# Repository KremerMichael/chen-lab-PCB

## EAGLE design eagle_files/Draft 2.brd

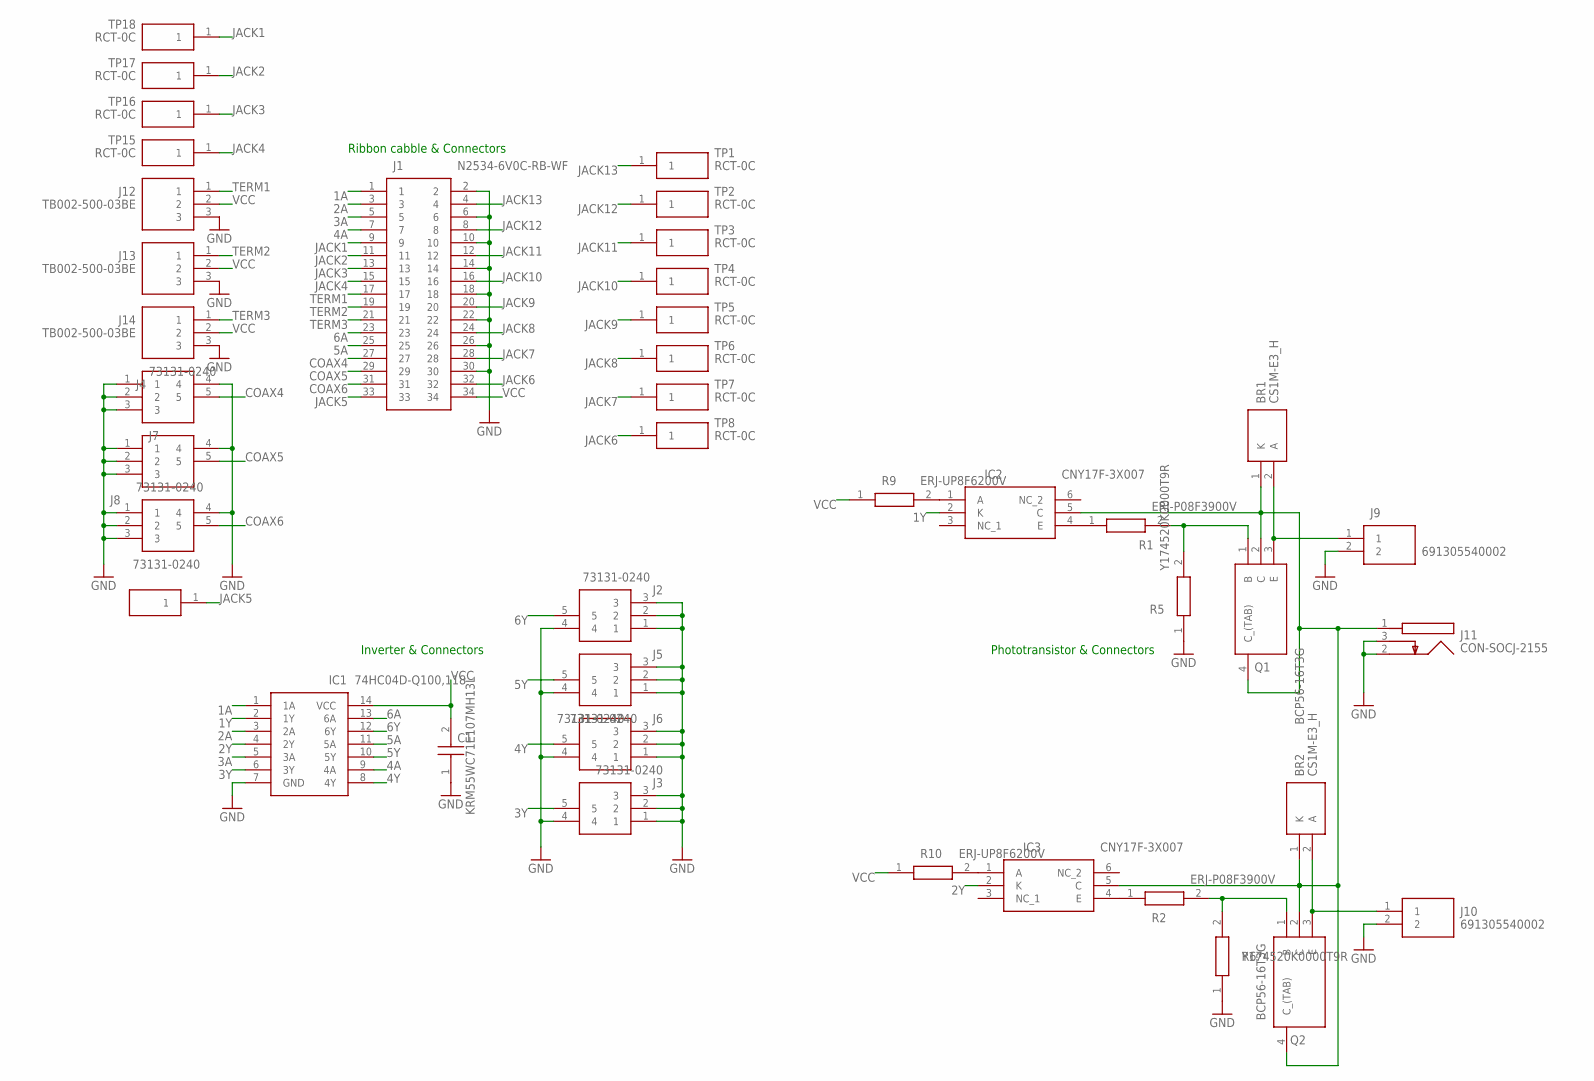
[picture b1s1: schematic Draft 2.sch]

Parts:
BR1, BR2: CS1M-E3_H; DIOM5127X229N
C1: KRM55WC71E107MH13L; CAPC6153X670N
IC1: 74HC04D-Q100,118; SOIC127P600X175-14N
IC2, IC3: CNY17F-3X007; SOP254P1030X440-6N
J1: N2534-6V0C-RB-WF; 3M_N2534-6V0C-RB-WF
J2, J3, J4, J5, J6, J7, J8: 73131-0240; 731310240
J9, J10: 691305540002; SHDRRA2W100P0X508_1X2_1216X120
J11: CON-SOCJ-2155; CONSOCJ2155
J12, J13, J14: TB002-500-03BE; SHDR3W100P0X500_1X3_1500X760X1
Q1, Q2: BCP56-16T3G; SOT230P700X175-4N
R1, R2: ERJ-P08F3900V; RESC3116X70N
R5, R6: Y174520K0000T9R; RESM6032X279N
R9, R10: ERJ-UP8F6200V; RESC3116X70N
TP1, TP2, TP3, TP4, TP5, TP6, TP7, TP8, TP9, TP15, TP16, TP17, TP18: RCT-0C

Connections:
1A: IC1.1 (1A), J1.1
1Y: IC1.2 (1Y), IC2.2 (K)
2A: IC1.3 (2A), J1.3
2Y: IC1.4 (2Y), IC3.2 (K)
3A: IC1.5 (3A), J1.5
3Y: IC1.6 (3Y), J3.5
4A: IC1.9 (4A), J1.7
4Y: IC1.8 (4Y), J6.5
5A: IC1.11 (5A), J1.25
5Y: IC1.10 (5Y), J5.5
6A: IC1.13 (6A), J1.23
6Y: IC1.12 (6Y), J2.5
COAX4: J1.27, J4.5
COAX5: J1.29, J7.5
COAX6: J1.31, J8.5
GND: C1.1, IC1.7 (GND), J1.2, J1.6, J1.10, J1.14, J1.18, J1.22, J1.26, J1.30, J2.1, J2.2, J2.3, J2.4, J3.1, J3.2, J3.3, J3.4, J4.1, J4.2, J4.3, J4.4, J5.1, J5.2, J5.3, J5.4, J6.1, J6.2, J6.3, J6.4, J7.1, J7.2, J7.3, J7.4, J8.1, J8.2, J8.3, J8.4, J9.2, J10.2, J11.2, J11.3, J12.3, J13.3, J14.3, R5.1, R6.1
JACK1: J1.9, TP18.1
JACK2: J1.11, TP17.1
JACK3: J1.13, TP16.1
JACK4: J1.15, TP15.1
JACK5: J1.33, TP9.1
JACK6: J1.32, TP8.1
JACK7: J1.28, TP7.1
JACK8: J1.24, TP6.1
JACK9: J1.20, TP5.1
JACK10: J1.16, TP4.1
JACK11: J1.12, TP3.1
JACK12: J1.8, TP2.1
JACK13: J1.4, TP1.1
unnamed: IC2.1 (A), R9.2
unnamed: BR2.2 (A), J10.1, Q2.3 (E)
unnamed: Q1.1 (B), R1.2, R5.2
unnamed: IC3.1 (A), R10.2
unnamed: IC3.4 (E), R2.1
unnamed: IC2.4 (E), R1.1
unnamed: BR1.2 (A), J9.1, Q1.3 (E)
unnamed: BR1.1 (K), BR2.1 (K), IC2.5 (C), IC3.5 (C), J11.1, Q1.2 (C), Q1.4 (C_(TAB)), Q2.2 (C), Q2.4 (C_(TAB))
unnamed: Q2.1 (B), R2.2, R6.2
TERM1: J1.17, J12.1
TERM2: J1.19, J13.1
TERM3: J1.21, J14.1
VCC: C1.2, IC1.14 (VCC), J1.34, J12.2, J13.2, J14.2, R9.1, R10.1

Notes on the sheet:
Ribbon cabble & Connectors
Inverter & Connectors
Phototransistor & Connectors

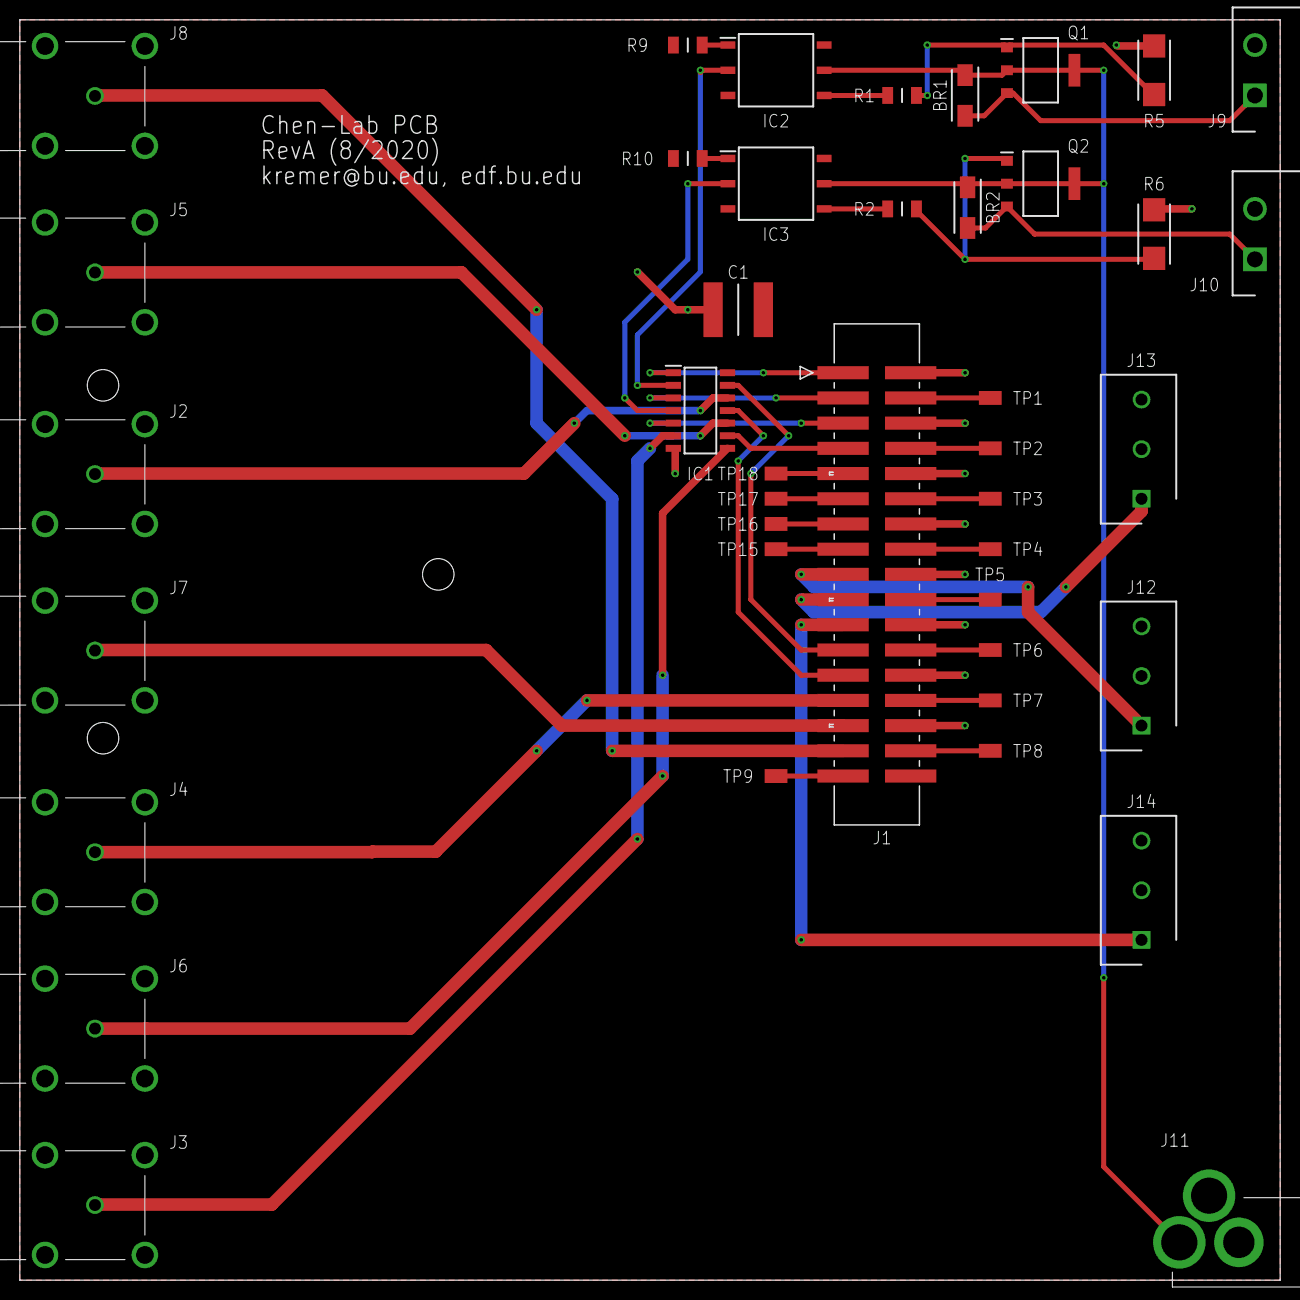
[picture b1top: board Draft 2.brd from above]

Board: 2 copper layers, 127.0 x 127.0 mm, 41 parts (0 on the bottom side), 42 nets.

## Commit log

2020-08-23 started git repo
2020-08-24 auto push run at Mon 24 Aug 2020 01:14:17 AM EDT
2020-08-24 auto push run at Mon 24 Aug 2020 11:25:32 AM EDT
2020-08-24 auto push run at Mon 24 Aug 2020 11:52:34 AM EDT
2020-08-24 auto push run at Mon 24 Aug 2020 11:56:28 AM EDT
2020-08-24 auto push run at Mon 24 Aug 2020 11:58:40 AM EDT
2020-08-24 auto push run at Mon 24 Aug 2020 12:03:22 PM EDT
2020-08-24 auto push run at Mon 24 Aug 2020 12:08:45 PM EDT
2020-08-24 auto push run at Mon 24 Aug 2020 12:14:02 PM EDT
2020-08-24 auto push run at Mon 24 Aug 2020 03:08:45 PM EDT
2020-08-24 auto push run at Mon 24 Aug 2020 03:10:38 PM EDT
2020-08-25 moving to kicad
2020-08-26 auto push run at Tue 25 Aug 2020 09:51:00 PM EDT
2020-08-26 auto push run at Tue 25 Aug 2020 09:53:13 PM EDT
2020-08-26 Add some 3D models
2020-08-26 more 3D models
2020-08-27 3D model for USB thing
2020-08-27 Add USB board with 3D
2020-08-27 Raise USB board to 0.75in height
2020-09-02 moved screw terminals and updated test points
2020-09-02 fixing schematic notes
2020-09-02 added BoM
2020-09-02 fixing 3d models hopefully
2020-09-03 added inch to board length and spaced out connectors more
2020-09-08 adding protocase files
2020-09-09 adding dimensions for protocase
2020-09-09 working on finishing enclosure
2020-09-16 working on resizing board
2020-09-17 working on fixing connectors
2020-09-17 moving stuff around and working on enclosure
2020-09-20 Finished cuts for panels
2020-09-23 adding BoM's for one off parts
2020-09-24 fixing BoM
2020-11-19 add revision docs
2020-12-02 Add ECO list
2020-12-02 add photo RevA
2020-12-02 edit ECOs
2020-12-02 Rev B mods
2020-12-02 Rev B changes to sch done?
2021-01-05 updating schematic, and moving PCB layout forward to RevB
2021-04-09 auto push run at Fri Apr 9 11:10:50 EDT 2021
2021-04-09 driver doc
2021-04-09 auto push run at Fri Apr 9 12:23:24 EDT 2021
2021-04-16 changin to right angle LEDs, fixing terminal blocks, fixing DC-DC footprint
2021-04-16 fixing 5v led
2021-04-23 auto push run at Fri Apr 23 09:52:58 EDT 2021
2021-04-23 new BoM
2021-04-27 migrating to branch with new BNC
2021-05-31 all done except moving J13
2021-05-31 Final Rev C layout
2021-05-31 Candidate Rev C gerbers
2021-05-31 Restore USB board footprint, tweak silkscreen
2021-06-09 Add Rev C BOM
2021-06-09 Final Rev C gerbers
2021-06-09 Fix a couple of BOM issues
